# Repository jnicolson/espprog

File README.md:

# ESP32 Programmer

This is a USB-C programmer for ESP32 chips, including autoreset as documented by espressif.  The pinout is compatible with the ESPFlash convention proposed by SuperHouse at https://www.superhouse.tv/espflash/ .

Additionally, 5V is exposed from the USB port (after the protection fuse) - this allows the ESP programmer to be used as a USB to serial module providing both 5V and 3.3V.  The 5V can either be connected via a jumper wire (if the programmer is mounted vertically) or directly via a pin (if mounted horizontally)

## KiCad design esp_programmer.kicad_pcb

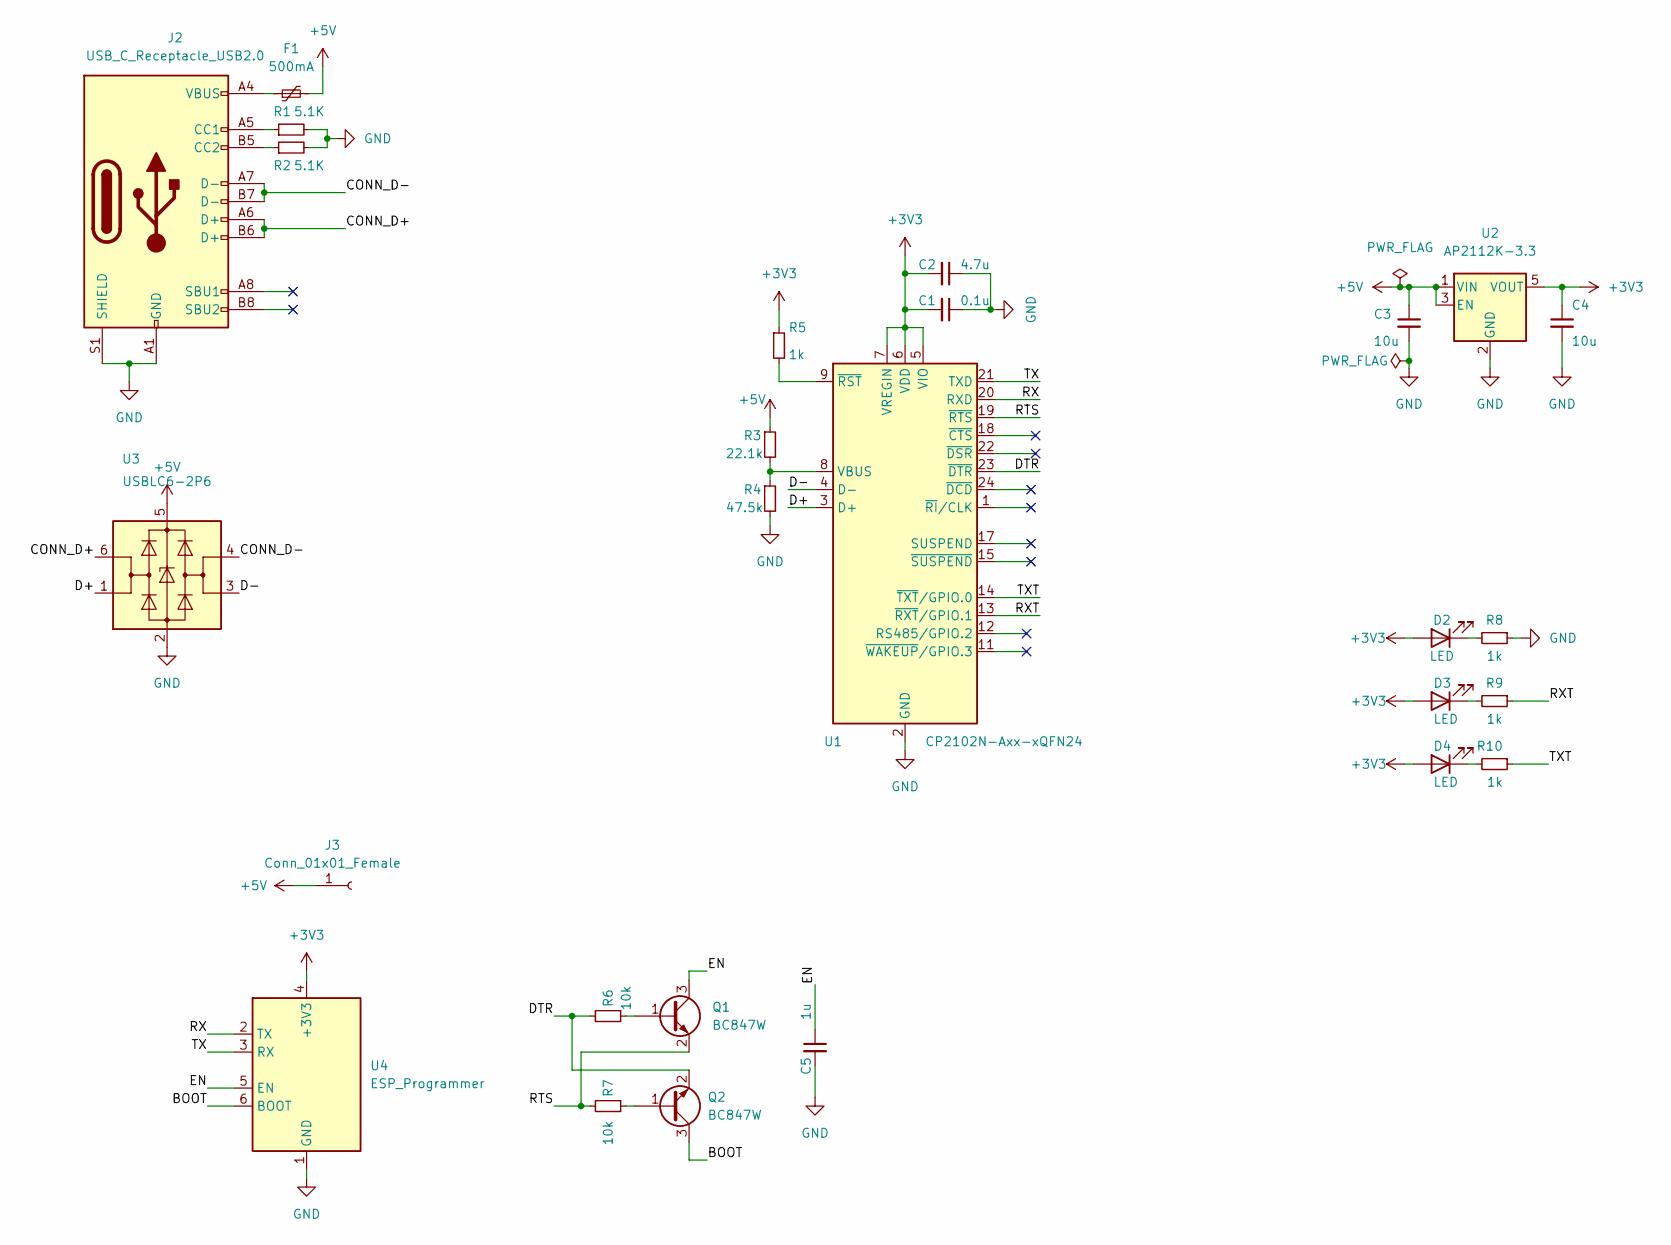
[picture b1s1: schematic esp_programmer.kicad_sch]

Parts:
C1: 0.1u; C_0603_1608Metric
C2: 4.7u; C_0603_1608Metric
C3, C4: 10u; C_0603_1608Metric
C5: 1u; C_0603_1608Metric
D2, D3, D4: LED; LED_0603_1608Metric
F1: 500mA; Fuse_1206_3216Metric
J2: USB_C_Receptacle_USB2.0; USB_C_Receptacle_HRO_TYPE-C-31-M-12
J3: Conn_01x01_Female; PinSocket_1x01_P2.54mm_Vertical
Q1, Q2: BC847W; SOT-323_SC-70
R1, R2: 5.1K; R_0603_1608Metric
R3: 22.1k; R_0603_1608Metric
R4: 47.5k; R_0603_1608Metric
R5, R8, R9, R10: 1k; R_0603_1608Metric
R6, R7: 10k; R_0603_1608Metric
U1: CP2102N-Axx-xQFN24; QFN-24-1EP_4x4mm_P0.5mm_EP2.6x2.6mm
U2: AP2112K-3.3; SOT-23-5
U3: USBLC6-2P6; SOT-666
U4: ESP_Programmer; PinHeader_1x06_P2.54mm_Vertical

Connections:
+3V3: C1.2, C2.2, C4.1, D2.2 (A), D3.2 (A), D4.2 (A), R5.1, U1.5 (VIO), U1.6 (VDD), U1.7 (VREGIN), U2.5 (VOUT), U4.4 (+3V3)
+5V: C3.1, F1.2, J3.1, R3.1, U2.1 (VIN), U2.3 (EN), U3.5 (VBUS)
/BOOT: Q2.3 (C), U4.6 (BOOT)
/CONN_D+: J2.A6 (D+), J2.B6 (D+), U3.6 (I/O1)
/CONN_D-: J2.A7 (D-), J2.B7 (D-), U3.4 (I/O2)
/D+: U1.3 (D+), U3.1 (I/O1)
/D-: U1.4 (D-), U3.3 (I/O2)
/DTR: Q2.2 (E), R6.2, U1.23 (~DTR)
/EN: C5.1, Q1.3 (C), U4.5 (EN)
/RTS: Q1.2 (E), R7.2, U1.19 (~RTS)
/RX: U1.20 (RXD), U4.2 (TX)
/RXT: R9.1, U1.13 (~RXT/GPIO.1)
/TX: U1.21 (TXD), U4.3 (RX)
/TXT: R10.1, U1.14 (~TXT/GPIO.0)
GND: C1.1, C2.1, C3.2, C4.2, C5.2, J2.A1 (GND), J2.A12 (GND), J2.B1 (GND), J2.B12 (GND), J2.S1 (SHIELD), R1.2, R2.2, R4.2, R8.1, U1.2 (GND), U1.25 (GND), U2.2 (GND), U3.2 (GND), U4.1 (GND)
unnamed: D2.1 (K), R8.2
unnamed: D3.1 (K), R9.2
unnamed: D4.1 (K), R10.2
unnamed: F1.1, J2.A4 (VBUS), J2.A9 (VBUS), J2.B4 (VBUS), J2.B9 (VBUS)
unnamed: J2.A5 (CC1), R1.1
unnamed: J2.B5 (CC2), R2.1
unnamed: Q1.1 (B), R6.1
unnamed: Q2.1 (B), R7.1
unnamed: R3.2, R4.1, U1.8 (VBUS)
unnamed: R5.2, U1.9 (~RST)

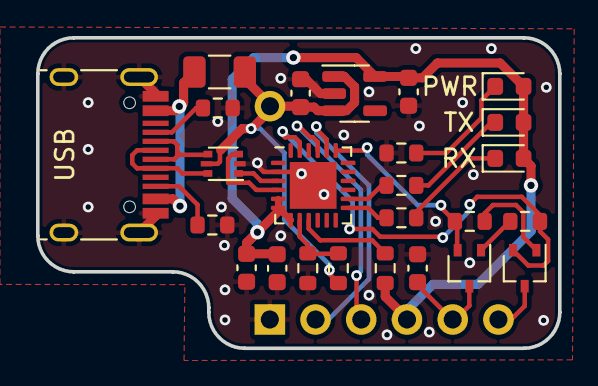
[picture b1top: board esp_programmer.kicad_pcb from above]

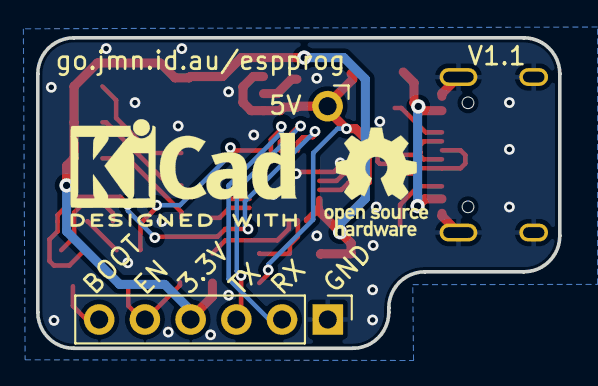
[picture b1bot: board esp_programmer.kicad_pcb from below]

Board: 2 copper layers, 29.0 x 17.2 mm, 27 parts (2 on the bottom side), 25 nets.

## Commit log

2021-10-04 Initial commit of README, LICENCE and gitignore
2021-10-04 Revision 1.1 - completed and working
